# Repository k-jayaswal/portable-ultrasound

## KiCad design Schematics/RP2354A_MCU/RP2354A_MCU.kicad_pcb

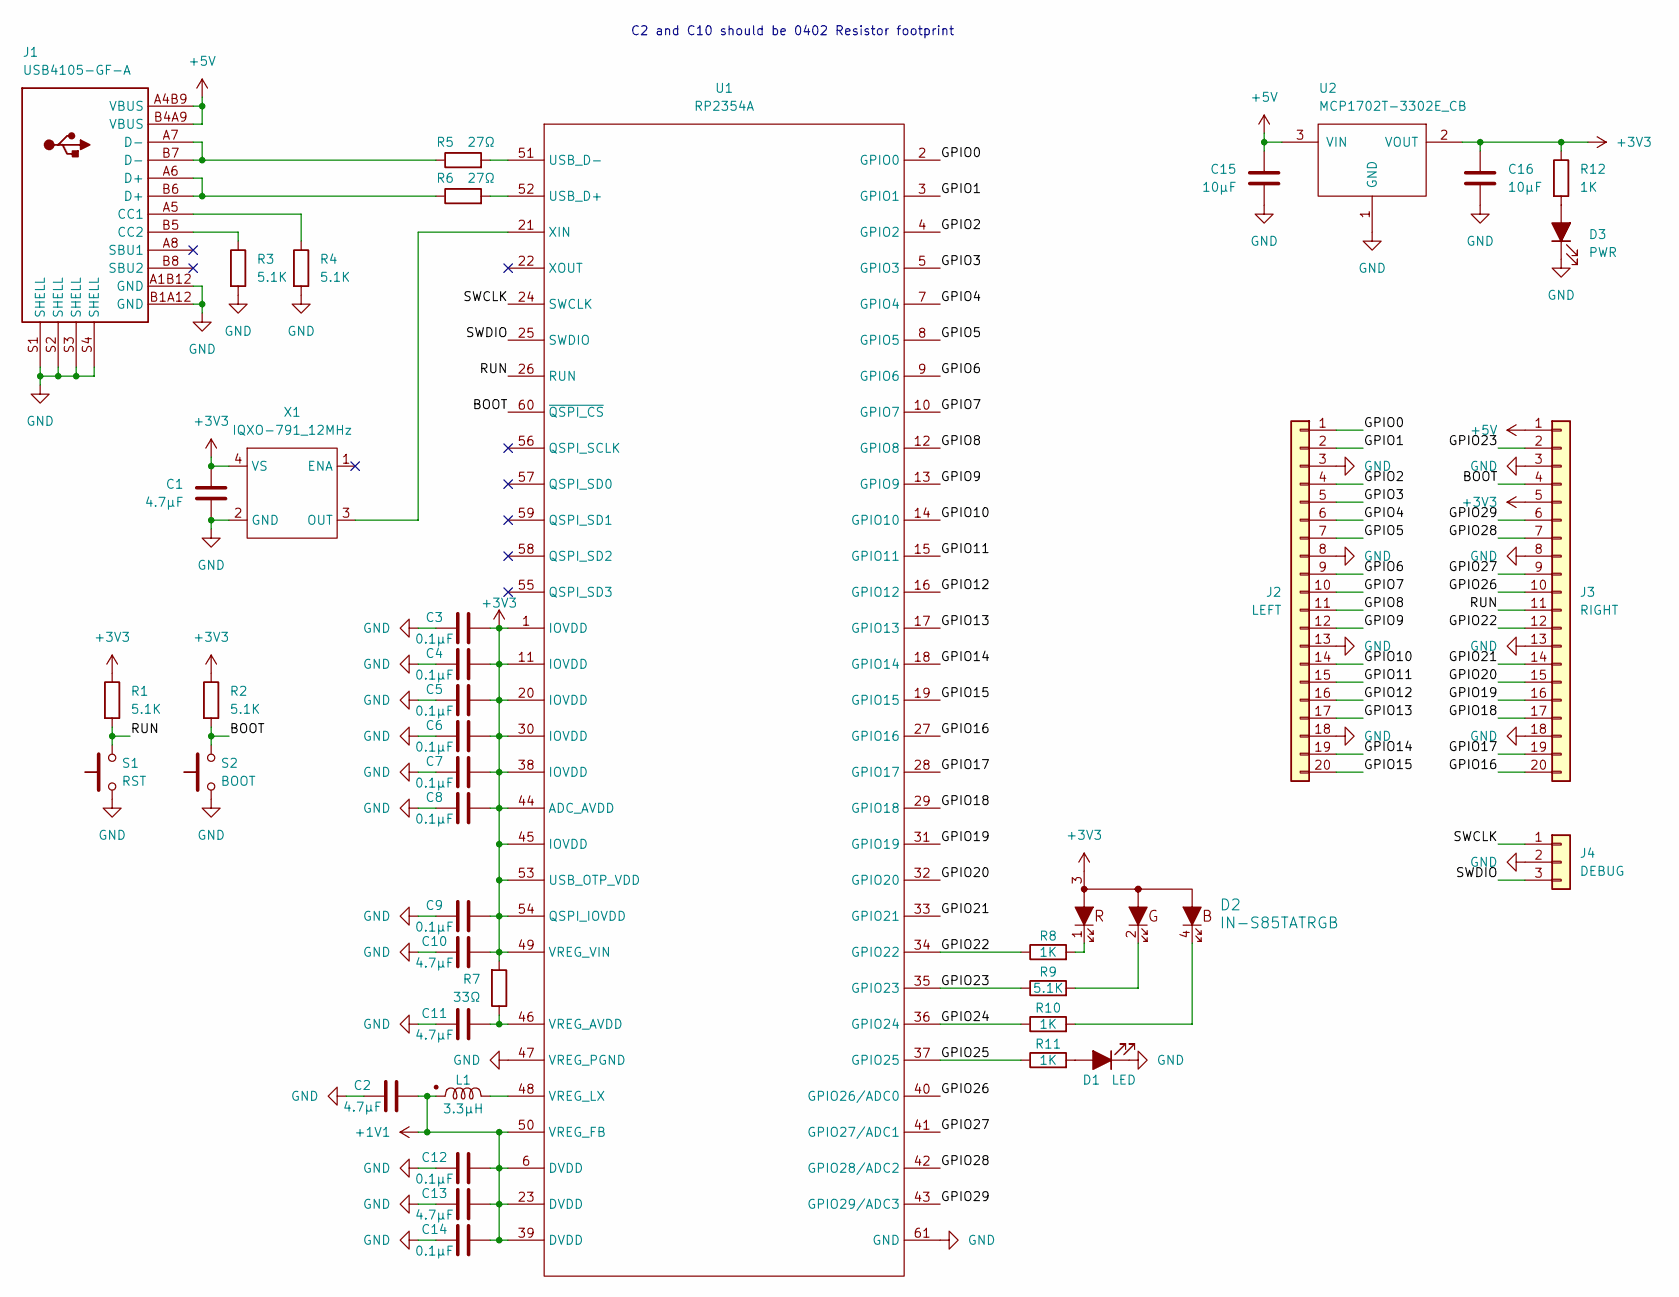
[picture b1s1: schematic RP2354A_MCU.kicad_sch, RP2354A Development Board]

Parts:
C1, C11, C13: 4.7µF; C_0402_1005Metric
C2, C10: 4.7µF; R_0402_1005Metric
C3, C4, C5, C6, C7, C8, C9, C12, C14: 0.1µF; C_0402_1005Metric
C15, C16: 10µF; C_0603_1608Metric
D1: LED; LED_0805_2012Metric
D2: IN-S85TATRGB
D3: PWR; LED_0805_2012Metric
J1: USB4105-GF-A
J2: LEFT; PinHeader_1x20_P2.54mm_Vertical
J3: RIGHT; PinHeader_1x20_P2.54mm_Vertical
J4: DEBUG; PinHeader_1x03_P2.54mm_Vertical
L1: 3.3µH; AOTA-B201610S3R3-101-T
R1, R2, R3, R4, R9: 5.1K; R_0402_1005Metric
R5, R6: 27Ω; R_0402_1005Metric
R7: 33Ω; R_0402_1005Metric
R8, R10, R11, R12: 1K; R_0402_1005Metric
S1: RST; SW_SPST_B3U-1000P
S2: BOOT; SW_SPST_B3U-1000P
U1: RP2354A; RP2350A_QFN-60_EP_7.75x7.75_Pitch0.4mm
U2: MCP1702T-3302E_CB; SOT-23A_MC_MCH
X1: IQXO-791_12MHz; IQXO-791

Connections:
+1V1: C2.2, C12.2, C13.2, C14.2, L1.1, U1.6 (DVDD), U1.23 (DVDD), U1.39 (DVDD), U1.50 (VREG_FB)
+3V3: C1.2, C3.2, C4.2, C5.2, C6.2, C7.2, C8.2, C9.2, C10.2, C16.1, D2.3, J3.5, R1.1, R2.1, R7.2, R12.1, U1.1 (IOVDD), U1.11 (IOVDD), U1.20 (IOVDD), U1.30 (IOVDD), U1.38 (IOVDD), U1.44 (ADC_AVDD), U1.45 (IOVDD), U1.49 (VREG_VIN), U1.53 (USB_OTP_VDD), U1.54 (QSPI_IOVDD), U2.2 (VOUT), X1.4 (VS); also elsewhere on the board
+5V: C15.2, J1.A4B9 (VBUS), J1.B4A9 (VBUS), J3.1, U2.3 (VIN)
/BOOT: J3.4, R2.2, S2.2, U1.60 (~QSPI_CS); also elsewhere on the board
/GPIO0: J2.1, U1.2 (GPIO0)
/GPIO1: J2.2, U1.3 (GPIO1)
/GPIO2: J2.4, U1.4 (GPIO2)
/GPIO3: J2.5, U1.5 (GPIO3)
/GPIO4: J2.6, U1.7 (GPIO4)
/GPIO5: J2.7, U1.8 (GPIO5)
/GPIO6: J2.9, U1.9 (GPIO6)
/GPIO7: J2.10, U1.10 (GPIO7)
/GPIO8: J2.11, U1.12 (GPIO8)
/GPIO9: J2.12, U1.13 (GPIO9)
/GPIO10: J2.14, U1.14 (GPIO10)
/GPIO11: J2.15, U1.15 (GPIO11)
/GPIO12: J2.16, U1.16 (GPIO12)
/GPIO13: J2.17, U1.17 (GPIO13)
/GPIO14: J2.19, U1.18 (GPIO14)
/GPIO15: J2.20, U1.19 (GPIO15)
/GPIO16: J3.20, U1.27 (GPIO16)
/GPIO17: J3.19, U1.28 (GPIO17)
/GPIO18: J3.17, U1.29 (GPIO18)
/GPIO19: J3.16, U1.31 (GPIO19)
/GPIO20: J3.15, U1.32 (GPIO20)
/GPIO21: J3.14, U1.33 (GPIO21)
/GPIO22: J3.12, R8.1, U1.34 (GPIO22)
/GPIO23: J3.2, R9.1, U1.35 (GPIO23)
/GPIO24: R10.1, U1.36 (GPIO24)
/GPIO25: R11.1, U1.37 (GPIO25)
/GPIO26: J3.10, U1.40 (GPIO26/ADC0)
/GPIO27: J3.9, U1.41 (GPIO27/ADC1)
/GPIO28: J3.7, U1.42 (GPIO28/ADC2)
/GPIO29: J3.6, U1.43 (GPIO29/ADC3)
/RUN: J3.11, R1.2, S1.2, U1.26 (RUN); also elsewhere on the board
/SWCLK: J4.1, U1.24 (SWCLK)
/SWDIO: J4.3, U1.25 (SWDIO)
GND: C1.1, C2.1, C3.1, C4.1, C5.1, C6.1, C7.1, C8.1, C9.1, C10.1, C11.1, C12.1, C13.1, C14.1, C15.1, C16.2, D1.1 (K), D3.1 (K), J1.A1B12 (GND), J1.B1A12 (GND), J1.S1 (SHELL), J1.S2 (SHELL), J1.S3 (SHELL), J1.S4 (SHELL), J2.3, J2.8, J2.13, J2.18, J3.3, J3.8, J3.13, J3.18, J4.2, R3.2, R4.2, S1.1, S2.1, U1.47 (VREG_PGND), U1.61 (GND), U2.1 (GND), X1.2 (GND); also elsewhere on the board
unnamed: D1.2 (A), R11.2
unnamed 39: D2.1, R8.2; also elsewhere on the board
unnamed 40: D2.2, R9.2; also elsewhere on the board
unnamed 41: D2.4, R10.2; also elsewhere on the board
unnamed 42: D3.2 (A), R12.2; also elsewhere on the board
unnamed: J1.A5 (CC1), R4.1
unnamed: J1.B5 (CC2), R3.1
unnamed: J1.A6 (D+), J1.B6 (D+), R6.1
unnamed: J1.A7 (D-), J1.B7 (D-), R5.1
unnamed: R6.2, U1.52 (USB_D+)
unnamed: R5.2, U1.51 (USB_D-)
unnamed: C11.2, R7.1, U1.46 (VREG_AVDD)
unnamed: L1.2, U1.48 (VREG_LX)
unnamed: U1.21 (XIN), X1.3 (OUT)

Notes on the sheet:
C2 and C10 should be 0402 Resistor footprint

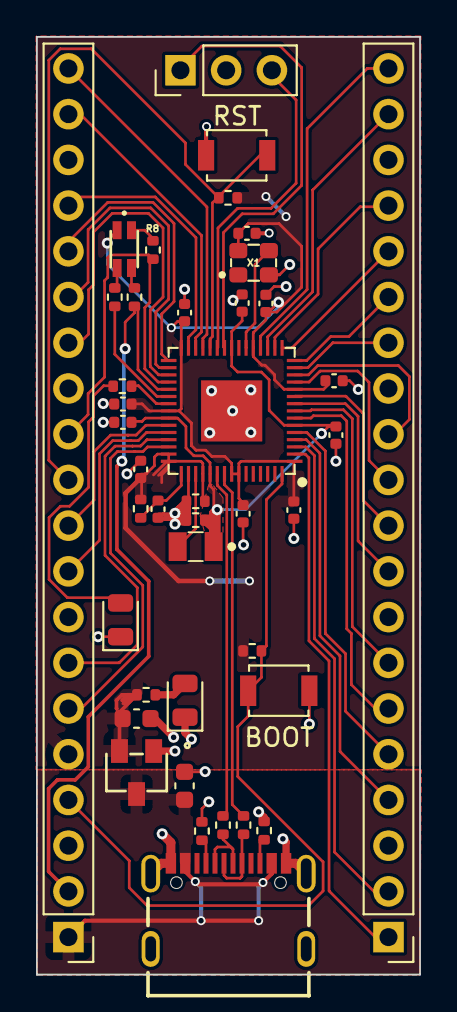
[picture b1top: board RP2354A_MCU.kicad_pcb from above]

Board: 2 copper layers, 21.3 x 52.1 mm, 42 parts (1 on the bottom side), 52 nets.

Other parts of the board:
BOOT: BOOT; SW_SPST_B3U-1000P
PWR: PWR; LED_0805_2012Metric
RGB: IN-S85TATRGB
RST: RST; SW_SPST_B3U-1000P
kibuzzard-6AD22F49: G***; kibuzzard-6AD22F49

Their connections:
+3V3: RGB.3; also elsewhere on the board
/BOOT: BOOT.2; also elsewhere on the board
/RUN: RST.2; also elsewhere on the board
GND: BOOT.1, PWR.1 (K), RST.1; also elsewhere on the board
unnamed 39: RGB.1; also elsewhere on the board
unnamed 40: RGB.2; also elsewhere on the board
unnamed 41: RGB.4; also elsewhere on the board
unnamed 42: PWR.2 (A); also elsewhere on the board
